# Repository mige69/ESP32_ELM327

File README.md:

# ESP32_ELM327
ELM327 emulator with an ESP32

Bluetooth function

OTA update function for a period of 10 minutes after power on

Apk file to android phone for suzuki bike work with ESP32_ELM327 (file work with elm327 with pic18f25k80)

folder eagle schematic

https://www.youtube.com/watch?v=ZsCw8m0fg5I

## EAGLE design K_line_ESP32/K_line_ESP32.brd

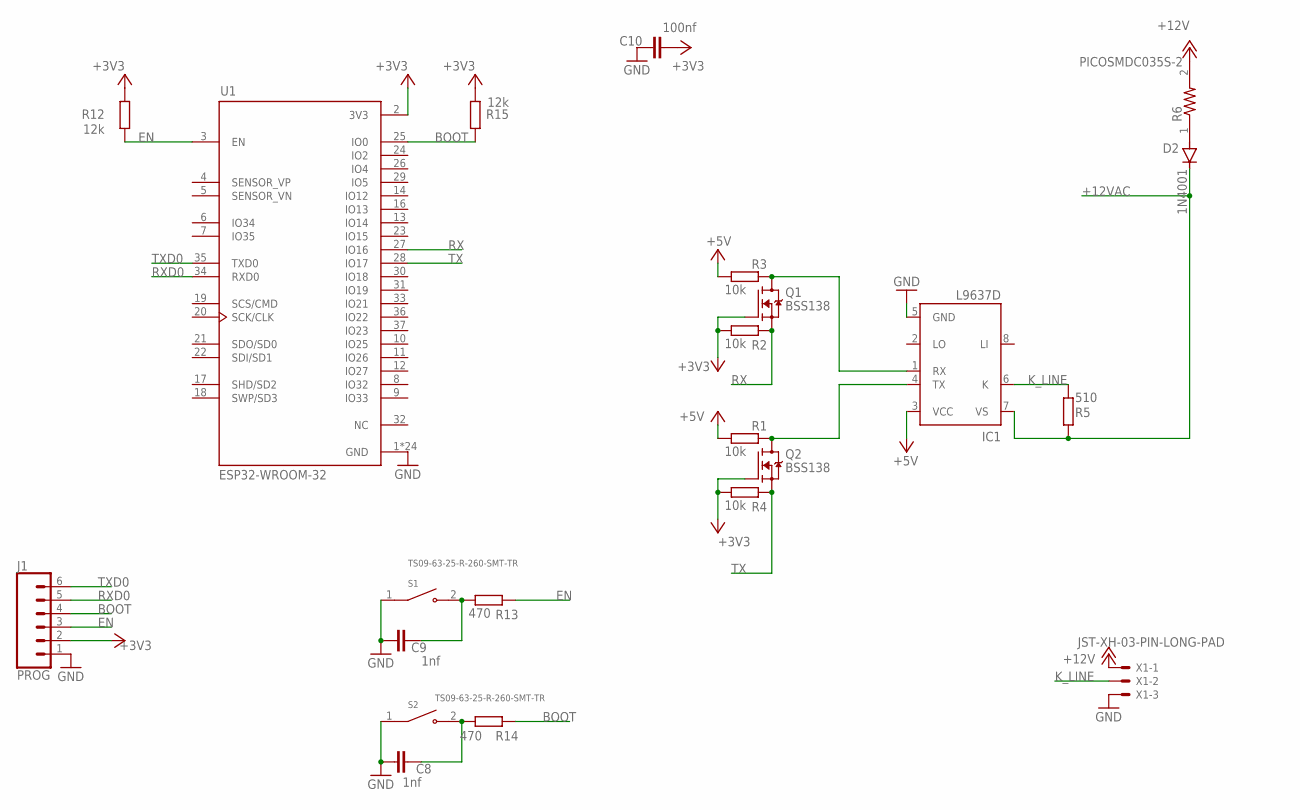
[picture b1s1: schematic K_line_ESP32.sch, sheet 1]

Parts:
C8, C9: 1nf; C0805K
C10: 100nf; C0805K
D2: 1N4001; DO214AA
IC1: L9637D; SO08
J1: PROG; 1X06
Q1, Q2: BSS138; SOT95P240X111-3N
R1, R2, R3, R4: 10k; R0805
R5: 510; R0805
R6: PICOSMDC035S-2; RESC2012X65N
R12, R15: 12k; R0805
R13, R14: 470; R0805
S1, S2: TS09-63-25-R-260-SMT-TR; SW_TS09-63-25-R-260-SMT-TR
U1: ESP32-WROOM-32; MODULE_ESP32-WROOM-32
X1: JST-XH-03-PIN-LONG-PAD; JST-XH-03-PACKAGE-LONG-PAD

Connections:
+3V3: C10.2, J1.2, Q1.1 (G), Q2.1 (G), R2.1, R4.1, R12.2, R15.2, U1.2 (3V3); also elsewhere on the board
+5V: IC1.3 (VCC), R1.1, R3.1; also elsewhere on the board
+12V: R6.2, X1.1
+12VAC: D2.C, IC1.7 (VS), R5.2; also elsewhere on the board
BOOT: J1.4, R14.1, R15.1, U1.25 (IO0)
EN: J1.3, R12.1, R13.1, U1.3 (EN)
GND: C8.2, C9.1, C10.1, IC1.5 (GND), J1.1, S1.1, S2.1, U1.1 (GND), U1.15 (GND), U1.38 (GND), U1.39_1 (GND), U1.39_2 (GND), U1.39_3 (GND), U1.39_4 (GND), U1.39_5 (GND), U1.39_6 (GND), U1.39_7 (GND), U1.39_8 (GND), U1.39_9 (GND), U1.39_10 (GND), U1.39_11 (GND), U1.39_12 (GND), U1.39_13 (GND), U1.39_14 (GND), U1.39_15 (GND), U1.39_16 (GND), U1.39_17 (GND), U1.39_18 (GND), U1.39_19 (GND), U1.39_20 (GND), U1.39_21 (GND), X1.3; also elsewhere on the board
K_LINE: IC1.6 (K), R5.1, X1.2
unnamed: IC1.1 (RX), Q1.3 (D), R3.2
unnamed: IC1.4 (TX), Q2.3 (D), R1.2
unnamed: D2.A, R6.1
unnamed: C8.1, R14.2, S2.2
unnamed: C9.2, R13.2, S1.2
RX: Q1.2 (S), R2.2, U1.27 (IO16)
RXD0: J1.5, U1.34 (RXD0)
TX: Q2.2 (S), R4.2, U1.28 (IO17)
TXD0: J1.6, U1.35 (TXD0)

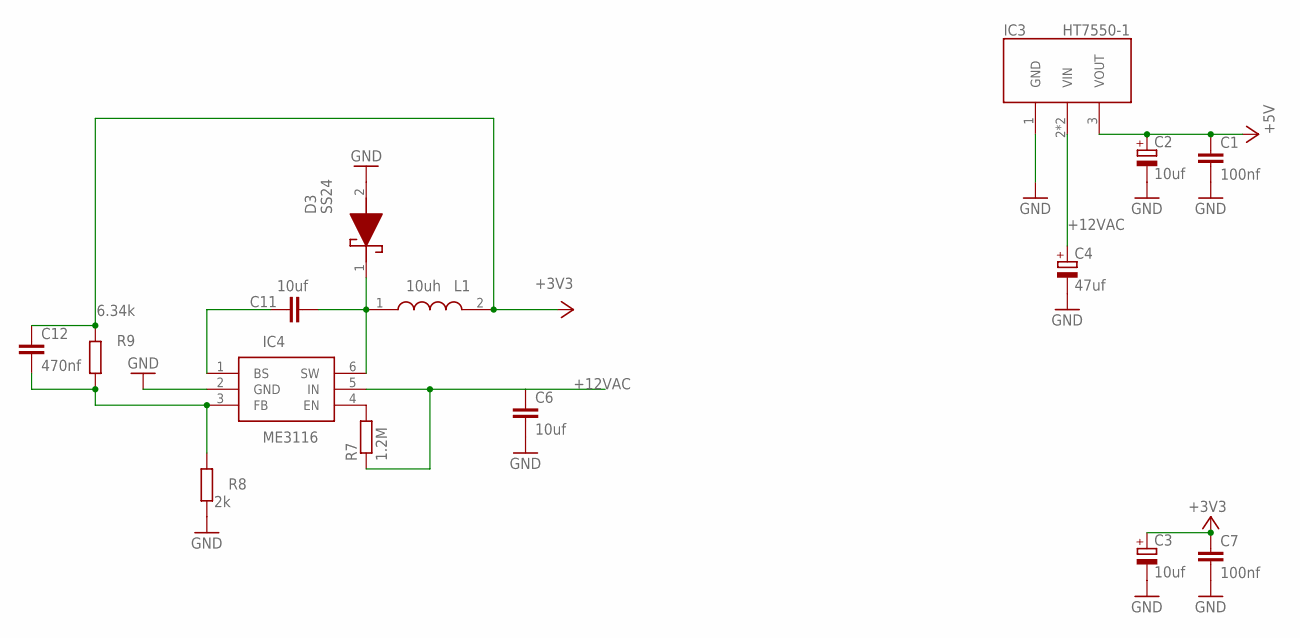
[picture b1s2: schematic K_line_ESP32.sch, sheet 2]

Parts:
C1, C7: 100nf; C0805K
C2, C3: 10uf; CT3216
C4: 47uf; CAPMP3528X210N
C6, C11: 10uf; C0805K
C12: 470nf; C0805K
D3: SS24; DIOM5436X247N
IC3: HT7550-1; SOT89
IC4: ME3116; SOT95P270X145-6N
L1: 10uh; INDPM7366X300N
R7: 1.2M; R0805
R8: 2k; R0805
R9: 6.34k; R0805

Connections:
+3V3: C3.+, C7.1, C12.1, L1.2, R9.2; also elsewhere on the board
+5V: C1.1, C2.+, IC3.3 (VOUT); also elsewhere on the board
+12VAC: C4.1 (+), C6.1, IC3.2 (VIN), IC3.2@1 (VIN), IC4.5 (IN), R7.1; also elsewhere on the board
GND: C1.2, C2.-, C3.-, C4.2 (-), C6.2, C7.2, D3.2 (A), IC3.1 (GND), IC4.2 (GND), R8.1; also elsewhere on the board
unnamed: IC4.4 (EN), R7.2
unnamed: C11.2, D3.1 (K), IC4.6 (SW), L1.1
unnamed: C11.1, IC4.1 (BS)
unnamed: C12.2, IC4.3 (FB), R8.2, R9.1

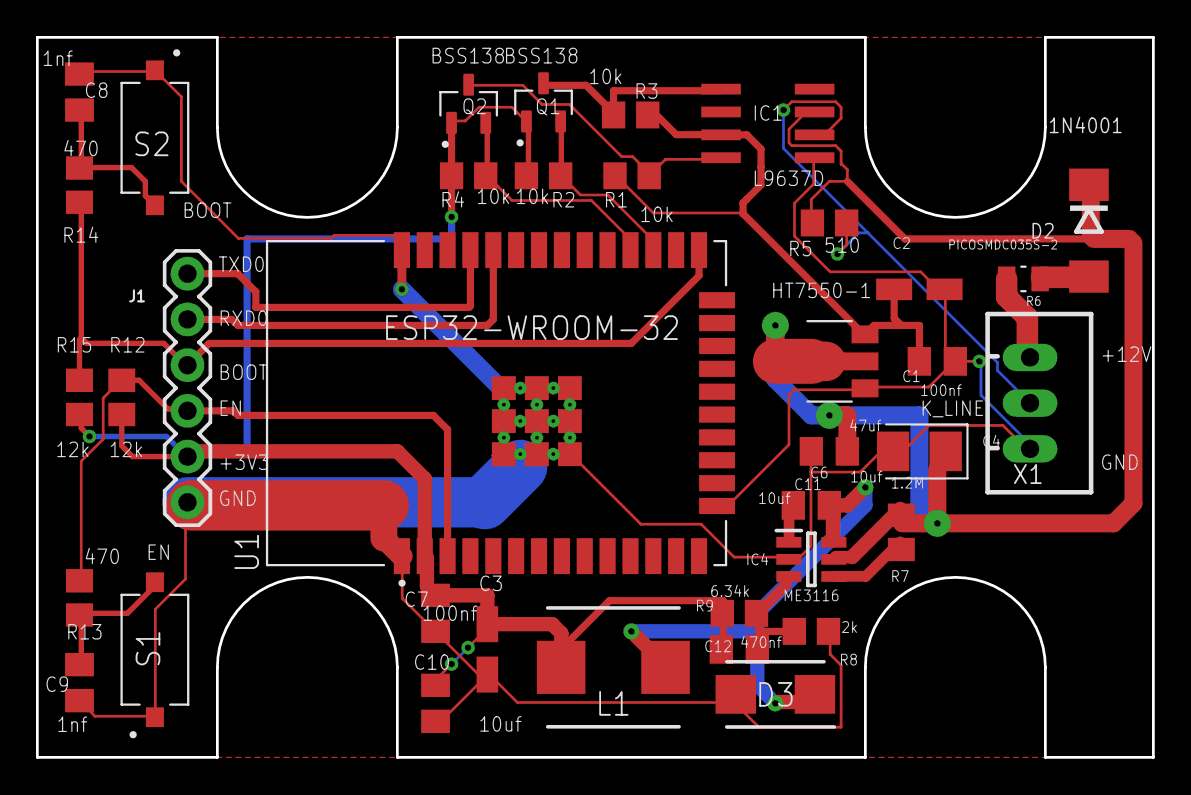
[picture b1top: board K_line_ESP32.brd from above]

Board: 2 copper layers, 62.0 x 40.0 mm, 37 parts (0 on the bottom side), 21 nets.

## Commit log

2025-03-10 Create EAGLE
2025-03-10 Rename EAGLE to ELM COMMAND
2025-03-10 Update ELM COMMAND

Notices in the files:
parts and their libraries:
SparkFun-Connectors: Licensing: Creative Commons ShareAlike 4.0 International - https://creativecommons.org/licenses/by-sa/4.0
